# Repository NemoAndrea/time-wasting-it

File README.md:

# *Time, wasting it* — a simple raspberry pi powered light clock

'Time, wasting-it' is a simple, raspberry pi-powered clock that uses **lights** instead of hands or digits to convey the time. At random points in time (configurable), the clock will show a playful light pattern. The demonstration and original build uses incandescent lights, but other types of lights can be used without modification.

> The project is a reimaging of the original artwork "*Time, wasting it...*" by **Bo Andrea**. The rebuilt version uses modern hardware to capture the original functionality, which was encoded by much lower level components. The main features (time to light method) and animations (random light patterns at random intervals) are carried over from this original art concept. The original description of the artwork was (in Dutch):
>
> "Koperdraad, buisgloeilampen, microprocessor. Meestal wordt slaafs de tijd aangegeven, zo nu en dan echter..."

The light clock synchronises with internet time, and hence will automatically adjust to winter and summer time. The clock runs a web interface that can be accessed via SSH and exposes manual controls to the user. A different time can be set, some of the config options can be seen at a glance, and an animation can be played back. The web interface also has a virtual mimic of the current clock lights (intensity/PWM) settings, which is handy for debugging if you are hooking up your own custom lights.

![[web interface screenshot]](img/web_interface.png)

### Assembly

Assembling your own clock is not very difficult, provided you have soldering tools, a bit of time, and basic SSH knowledge. 

Briefly, you will need the following components

1. Raspberry pi zero (any variant will do, but a version with wireless connectivity is strongly recommended)
2. The project PCB, which can be ordered online using the `gerber` files in this repository
3. A power supply that has enough power to run your lights of choice
4. A buck converter, if your lights of choice do not run at 5V (the raspberry pi will need 5V)
5. 12 primary lights, that will convey the time. *must be PWM dimmable*
6. Wires, through-hole components and soldering tools

For a more detailed list of the required components and assembly guide, consult [the hardware setup section 📖](./docs/hardware.md)

### Software setup & usage

The software setup for the project (assuming the hardware is assembled and ready)  and configuration starts with the cloning of this repository onto the Raspberry Pi, and then a few simple commands, outlined in greater detail in [the software setup section 📖](./docs/software.md).

> The code is all JavaScript, which at the time was chosen for easy interfacing with the web UI. 

### Project state

The project is complete, and is no longer seeing active development. A running version of the light clock is operational, and has been reliable in use for almost a year (as of time of writing).

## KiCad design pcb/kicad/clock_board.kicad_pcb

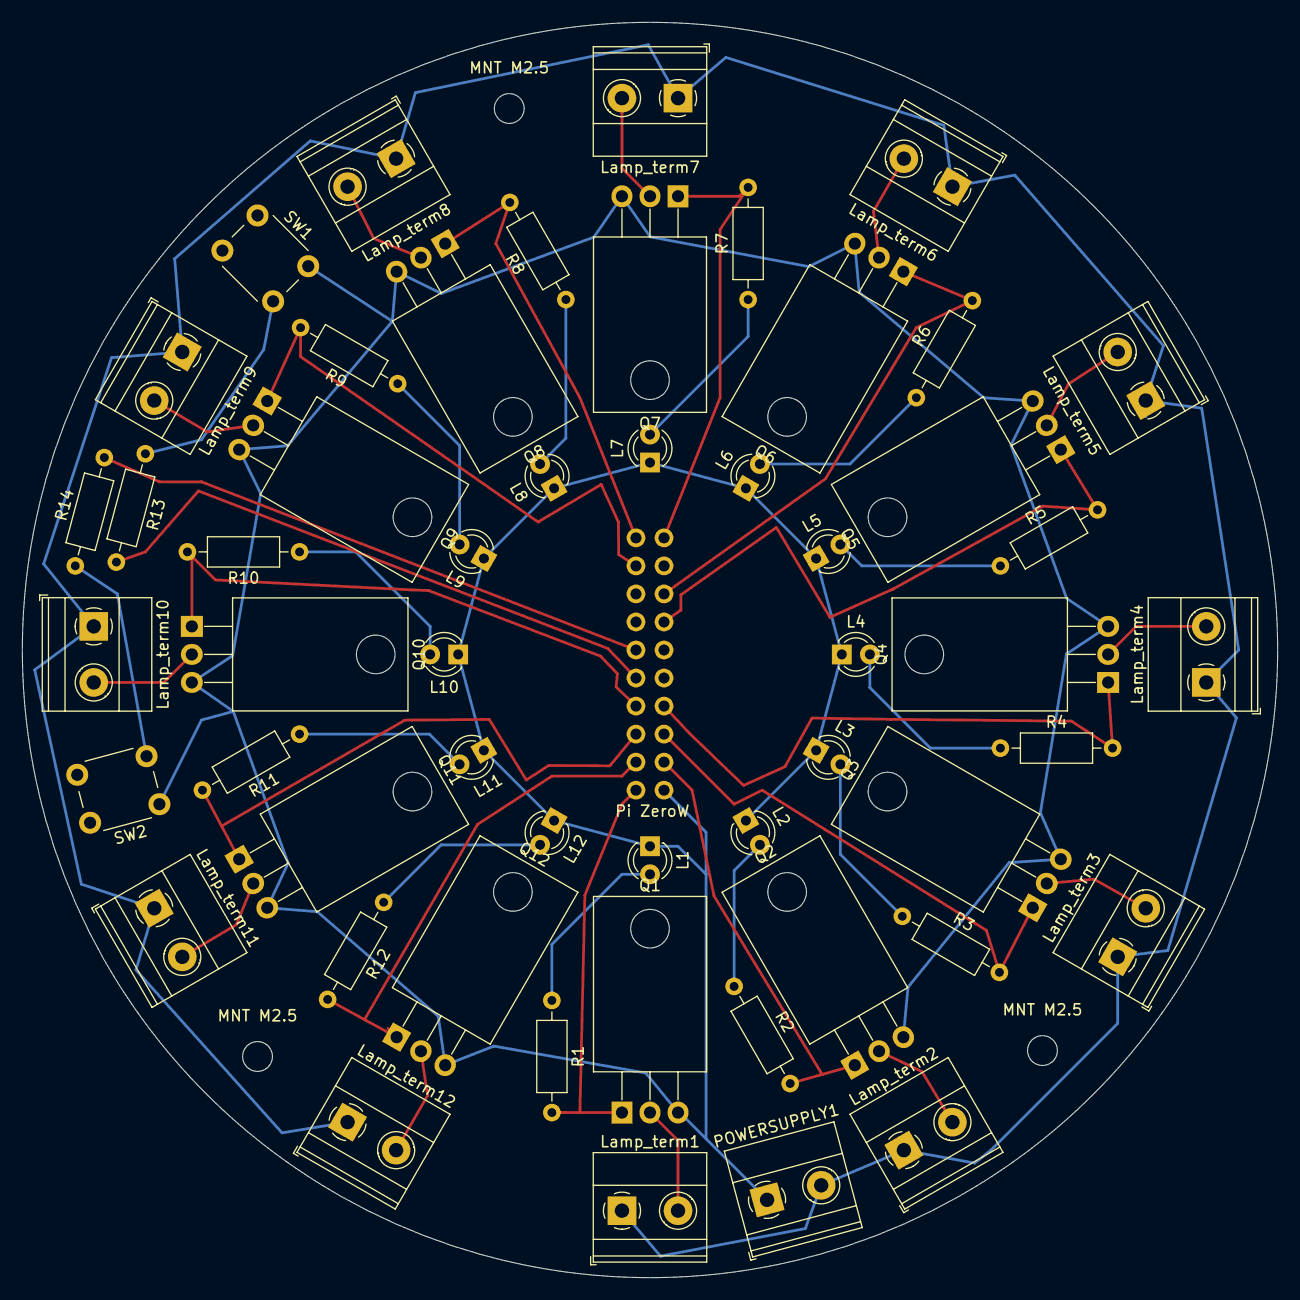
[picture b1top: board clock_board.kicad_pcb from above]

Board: 2 copper layers, 113.7 x 113.7 mm, 57 parts (0 on the bottom side), 7 nets.

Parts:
L1, L2, L3, L4, L5, L6, L7, L8, L9, L10, L11, L12: LED; LED_D3.0mm
Lamp_term1, Lamp_term2, Lamp_term3, Lamp_term4, Lamp_term5, Lamp_term6, Lamp_term7, Lamp_term8, Lamp_term9, Lamp_term10, Lamp_term11, Lamp_term12: 12V; TerminalBlock_Phoenix_MKDS-1,5-2-5.08_1x02_P5.08mm_Horizont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
MNT M2.5, MNT M2.5#2, MNT M2.5#3: MountingHole_2.7mm_M2.5
POWERSUPPLY1: 12V; TerminalBlock_Phoenix_MKDS-1,5-2-5.08_1x02_P5.08mm_Horizont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
Pi ZeroW: Raspberry_Pi_Zero_for_clock
Q1, Q2, Q3, Q4, Q5, Q6, Q7, Q8, Q9, Q10, Q11, Q12: IRLZ44N; TO-220-3_Horizontal_TabDown
R1, R2, R3, R4, R5, R6, R7, R8, R9, R10, R11, R12: 500ohm; R_Axial_DIN0207_L6.3mm_D2.5mm_P10.16mm_Horizontal
R13, R14: 1k; R_Axial_DIN0207_L6.3mm_D2.5mm_P10.16mm_Horizontal
SW1, SW2: SW_Push; SW_PUSH_6mm

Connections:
+12V: Lamp_term1.1, Lamp_term2.1, Lamp_term3.1, Lamp_term4.1, Lamp_term5.1, Lamp_term6.1, Lamp_term7.1, Lamp_term8.1, Lamp_term9.1, Lamp_term10.1, Lamp_term11.1, Lamp_term12.1, POWERSUPPLY1.2
GND: L1.1, L2.1, L3.1, L4.1, L5.1, L6.1, L7.1, L8.1, L9.1, L10.1, L11.1, L12.1, POWERSUPPLY1.1, Pi ZeroW.25, Q1.3, Q2.3, Q3.3, Q4.3, Q5.3, Q6.3, Q7.3, Q8.3, Q9.3, Q10.3, Q11.3, Q12.3, SW1.1, SW2.1
unnamed: Q8.1, R8.2
unnamed: L1.2, L2.2, L3.2, L4.2, L5.2, L6.2, L7.2, L8.2, L9.2, L10.2, L11.2, L12.2, R1.1, R2.1, R3.1, R4.1, R5.1, R6.1, R7.1, R8.1, R9.1, R10.1, R11.1, R12.1
unnamed: Lamp_term1.2, Lamp_term2.2, Lamp_term3.2, Lamp_term4.2, Lamp_term5.2, Lamp_term6.2, Lamp_term7.2, Lamp_term8.2, Lamp_term9.2, Lamp_term10.2, Lamp_term11.2, Lamp_term12.2, Q1.2, Q2.2, Q3.2, Q4.2, Q5.2, Q6.2, Q7.2, Q8.2, Q9.2, Q10.2, Q11.2, Q12.2
unnamed: R13.1, SW1.2
unnamed: R14.1, SW2.2

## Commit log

2021-07-05 First version frontend
2021-07-05 Moving to proper classes and basic UI
2021-07-10 Notes
    Adding some notes about power draw and heating
2021-07-10 Added basic GPIO to LightClock class
2021-07-11 UI and logic update
    Added manual time implementation to interface and tested with hardware. Tried to make everything as linked as possible.
2021-07-16 First implementation of animations
    Play a rarndom animation from list of animations. Will not play the last played animation again. Animations currently based off frames, rather than time. Added seconds precision to SimpleTime
2021-07-17 Interface and Animation update
    Big improvements to UI with ability to start animations from list, and see status of the clock. Animations improved with LightArray object.
2021-07-21 Refactoring & Moving to config
    Project refactoring and moving configuration to a separate config file
2021-07-31 Animation & Button update
    Add basic button support for default project PCB. Add more animations. Properly support maxPWM for animations. Minor interface updates to enable longer list of animations. Added option to reverse GPI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
2021-08-01 Cleanup repository
    Reorganising the files in the repository and removing some old files that no longer serve a purpose
2021-08-15 Fixed array mirroring
2021-10-10 Add night mode & new animations
    Turned off some some animatinos that dont work well with the hardware and added new one. Added primitive night mode, to dim lights at night.
2021-10-31 Auto-boot instructions
    Added instructions in readme to auto-start the clock upon boot.
2022-08-16 Improve documentation
    Move towards a public release
2022-08-18 Add gerber and kicad source files
    Added the raw gerber files for fab and the kicad source files used for board design.
2022-08-20 Add hardware assembly instructions and docs
    Added the hardware assembly instructions, some more images, and 3D printable part.
2022-08-20 Fix readme
